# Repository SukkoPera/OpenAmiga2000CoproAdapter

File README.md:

# OpenAmiga2000CoproAdapter
OpenAmiga2000CoproAdapter is an Open Hardware adapter that allows installing the main processor of a Commodore Amiga 2000 computer in the co-processor slot.

### Summary
OpenAmiga2000CoproAdapter is an adapter that allows installing the main processor of a Commodore Amiga 2000 computer in the co-processor slot, based on [work by kipper2k](http://eab.abime.net/showthread.php?t=89604). It is mainly useful to mount TerribleFire and other accelerator cards without having to remove the floppy drive tray and without having them bump into your MegaChip, in case.

The adapter is very similar to the original, except that I skipped the INT7 and the A600 NMI circuits. Those are not needed for TerribleFire cards and for most other boards (I think they are for Vampires only). I carried over the INT2/OVR header, since the former is needed for the TF530. I have also introduced solder jumpers for the FR0-2 signals: those are not connected on kipper2k's board, I don't know why and it works well anyway, but I thought they wouldn't hurt as they will be open by default.

You may be able to install this without removing the original CPU by cutting the E jumper and closing the BOSS one.

This is a slightly expensive board to manufacture because it exceeds the 10x10cm limit that cheap fab houses impose, because it needs gold-plating for better contact and resistance to repeated insertions/removals, and because the edge connector should be beveled to ease insertion. These are the recommended settings if you want to get the boards made.

### Installation
**Please be very careful when plugging this board** in the co-processor slot: there is an arrow on the board, **it must point to the back of the Amiga**. Plugging this adapter backwards will damage your CPU/accelerator card, as some pins of the CPU slot carry +12V!

When this board is installed, most likely the original 68000 socket must be left empty unless you cut the E jumper and close the BOSS jumper, though this ultimately depends on the particular card you will be installing.

### License
The OpenAmiga2000CoproAdapter documentation, including the design itself, is copyright &copy; SukkoPera 2018-2019.

OpenAmiga2000CoproAdapter is Open Hardware licensed under the [CERN OHL v. 1.2](http://ohwr.org/cernohl).

You may redistribute and modify this documentation under the terms of the CERN OHL v.1.2. This documentation is distributed *as is* and WITHOUT ANY EXPRESS OR IMPLIED WARRANTIES whatsoever with respect to its functionality, operability or use, including, without limitation, any implied warranties OF MERCHANTABILITY, SATISFACTORY QUALITY, FITNESS FOR A PARTICULAR PURPOSE or infringement. We expressly disclaim any liability whatsoever for any direct, indirect, consequential, incidental or special damages, including, without limitation, lost revenues, lost profits, losses resulting from business interruption or loss of data, regardless of the form of action or legal theory under which the liability may be asserted, even if advised of the possibility or likelihood of such damages.

A copy of the full license is included in file [LICENSE.pdf](LICENSE.pdf), please refer to it for applicable conditions. In order to properly deal with its terms, please see file [LICENSE_HOWTO.pdf](LICENSE_HOWTO.pdf).

The contact points for information about manufactured Products (see section 4.2) are listed in file [PRODUCT.md](PRODUCT.md).

Any modifications made by Licensees (see section 3.4.b) shall be recorded in file [CHANGES.md](CHANGES.md).

The Documentation Location of the original project is https://github.com/SukkoPera/OpenAmiga2000CoproAdapter/.

### Support the Project
Since the project is open you are free to get the PCBs made by your preferred manufacturer, however in case you want to support the development, you can order them from PCBWay through this link:

You get cheap, professionally-made and good quality PCBs, I get some credit that will help with this and [other projects](https://www.pcbway.com/project/member/shareproject/?bmbid=41100). You won't even have to worry about the various PCB options, it's all pre-configured for you!

Also, if you still have to register to that site, [you can use this link](https://www.pcbway.com/setinvite.aspx?inviteid=41100) to get some bonus initial credit (and yield me some more).

Again, if you want to use another manufacturer, feel free to, don't feel obligated :). But then you can buy me a coffee if you want:

### Get Help
If you need help or have questions, you can join [the official Telegram group](https://t.me/joinchat/HUHdWBC9J9JnYIrvTYfZmg).

### Thanks
Thanks to kipper2k, of course :).

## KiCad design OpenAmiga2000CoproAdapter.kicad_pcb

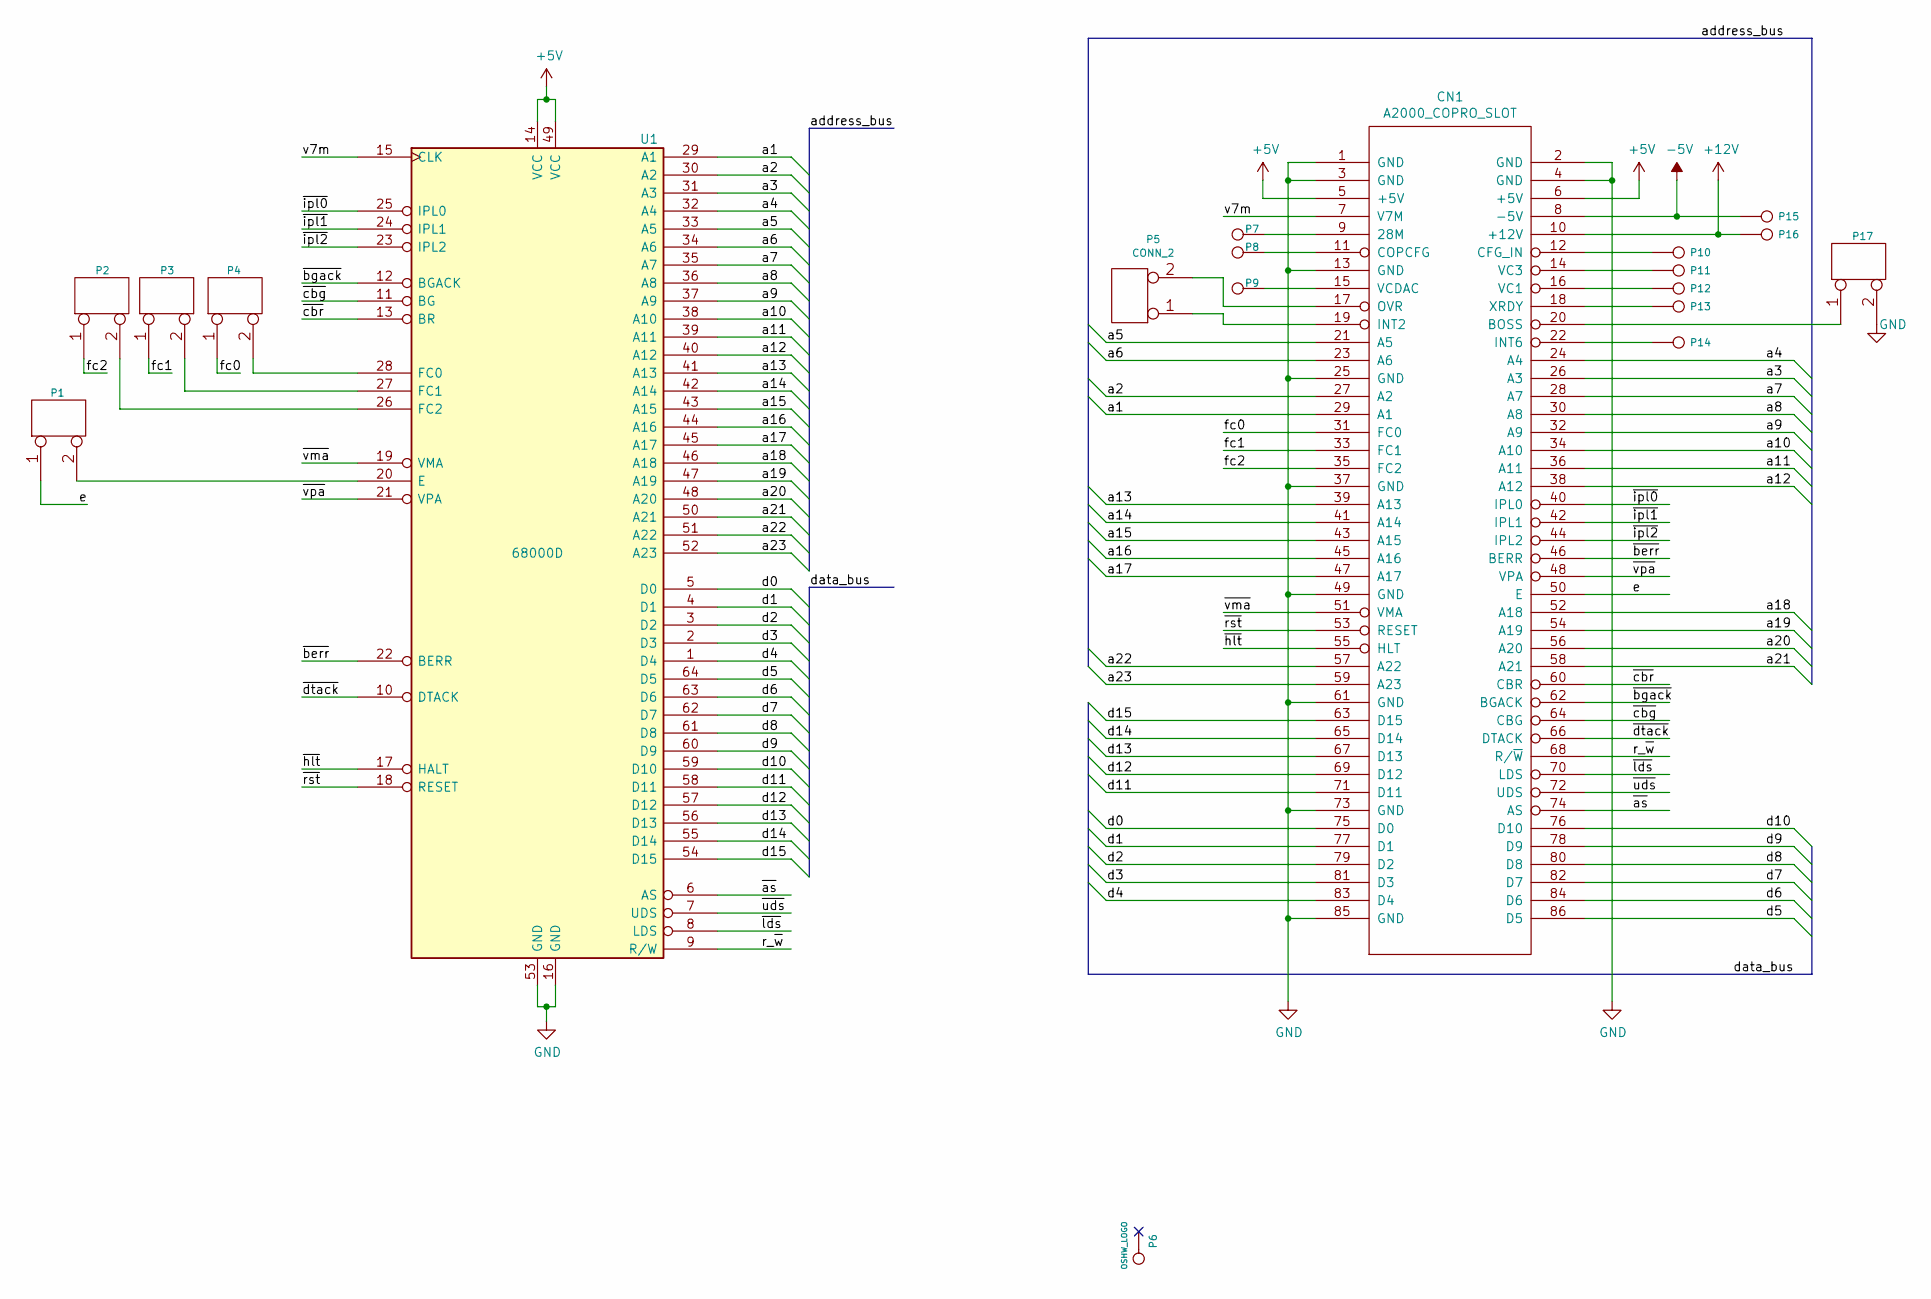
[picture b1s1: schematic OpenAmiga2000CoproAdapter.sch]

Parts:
CN1: A2000_COPRO_SLOT
P1: CONN_2; SolderJumper-2_P1.3mm_Bridged_RoundedPad1.0x1.5mm
P2, P3, P4, P17: CONN_2; SolderJumper-2_P1.3mm_Open_RoundedPad1.0x1.5mm
P5: CONN_2; PinHeader_1x02_P2.54mm_Vertical
P6: OSHW_LOGO; OSHW-Logo_7.5x8mm_Copper
P7, P8, P9, P10, P11, P12, P13, P14, P15, P16: CONN_1; TestPoint_Pad_D1.5mm
U1: 68000D; DIP-64_W22.86mm_Socket_LongPads

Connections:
+5V: CN1.5 (+5V), CN1.6 (+5V), U1.14 (VCC), U1.49 (VCC)
+12V: CN1.10 (+12V), P16.1
-5V: CN1.8 (-5V), P15.1
/a1: CN1.29 (A1), U1.29 (A1)
/a2: CN1.27 (A2), U1.30 (A2)
/a3: CN1.26 (A3), U1.31 (A3)
/a4: CN1.24 (A4), U1.32 (A4)
/a5: CN1.21 (A5), U1.33 (A5)
/a6: CN1.23 (A6), U1.34 (A6)
/a7: CN1.28 (A7), U1.35 (A7)
/a8: CN1.30 (A8), U1.36 (A8)
/a9: CN1.32 (A9), U1.37 (A9)
/a10: CN1.34 (A10), U1.38 (A10)
/a11: CN1.36 (A11), U1.39 (A11)
/a12: CN1.38 (A12), U1.40 (A12)
/a13: CN1.39 (A13), U1.41 (A13)
/a14: CN1.41 (A14), U1.42 (A14)
/a15: CN1.43 (A15), U1.43 (A15)
/a16: CN1.45 (A16), U1.44 (A16)
/a17: CN1.47 (A17), U1.45 (A17)
/a18: CN1.52 (A18), U1.46 (A18)
/a19: CN1.54 (A19), U1.47 (A19)
/a20: CN1.56 (A20), U1.48 (A20)
/a21: CN1.58 (A21), U1.50 (A21)
/a22: CN1.57 (A22), U1.51 (A22)
/a23: CN1.59 (A23), U1.52 (A23)
/d0: CN1.75 (D0), U1.5 (D0)
/d1: CN1.77 (D1), U1.4 (D1)
/d2: CN1.79 (D2), U1.3 (D2)
/d3: CN1.81 (D3), U1.2 (D3)
/d4: CN1.83 (D4), U1.1 (D4)
/d5: CN1.86 (D5), U1.64 (D5)
/d6: CN1.84 (D6), U1.63 (D6)
/d7: CN1.82 (D7), U1.62 (D7)
/d8: CN1.80 (D8), U1.61 (D8)
/d9: CN1.78 (D9), U1.60 (D9)
/d10: CN1.76 (D10), U1.59 (D10)
/d11: CN1.71 (D11), U1.58 (D11)
/d12: CN1.69 (D12), U1.57 (D12)
/d13: CN1.67 (D13), U1.56 (D13)
/d14: CN1.65 (D14), U1.55 (D14)
/d15: CN1.63 (D15), U1.54 (D15)
/e: CN1.50 (E), P1.1
/fc0: CN1.31 (FC0), P4.1
/fc1: CN1.33 (FC1), P3.1
/fc2: CN1.35 (FC2), P2.1
/r_~w: CN1.68 (R/~W), U1.9 (R/W)
/v7m: CN1.7 (V7M), U1.15 (CLK)
/~as: CN1.74 (AS), U1.6 (AS)
/~berr: CN1.46 (BERR), U1.22 (BERR)
/~bgack: CN1.62 (BGACK), U1.12 (BGACK)
/~cbg: CN1.64 (CBG), U1.11 (BG)
/~cbr: CN1.60 (CBR), U1.13 (BR)
/~dtack: CN1.66 (DTACK), U1.10 (DTACK)
/~hlt: CN1.55 (HLT), U1.17 (HALT)
/~ipl0: CN1.40 (IPL0), U1.25 (IPL0)
/~ipl1: CN1.42 (IPL1), U1.24 (IPL1)
/~ipl2: CN1.44 (IPL2), U1.23 (IPL2)
/~lds: CN1.70 (LDS), U1.8 (LDS)
/~rst: CN1.53 (RESET), U1.18 (RESET)
/~uds: CN1.72 (UDS), U1.7 (UDS)
/~vma: CN1.51 (VMA), U1.19 (VMA)
/~vpa: CN1.48 (VPA), U1.21 (VPA)
GND: CN1.1 (GND), CN1.2 (GND), CN1.3 (GND), CN1.4 (GND), CN1.13 (GND), CN1.25 (GND), CN1.37 (GND), CN1.49 (GND), CN1.61 (GND), CN1.73 (GND), CN1.85 (GND), P17.2 (PM), U1.16 (GND), U1.53 (GND)
unnamed: CN1.9 (28M), P7.1
unnamed: CN1.11 (COPCFG), P8.1
unnamed: CN1.12 (CFG_IN), P10.1
unnamed: CN1.14 (VC3), P11.1
unnamed: CN1.15 (VCDAC), P9.1
unnamed: CN1.16 (VC1), P12.1
unnamed: CN1.17 (OVR), P5.2 (PM)
unnamed: CN1.18 (XRDY), P13.1
unnamed: CN1.19 (INT2), P5.1
unnamed: CN1.20 (BOSS), P17.1
unnamed: CN1.22 (INT6), P14.1
unnamed: P1.2 (PM), U1.20 (E)
unnamed: P2.2 (PM), U1.26 (FC2)
unnamed: P3.2 (PM), U1.27 (FC1)
unnamed: P4.2 (PM), U1.28 (FC0)

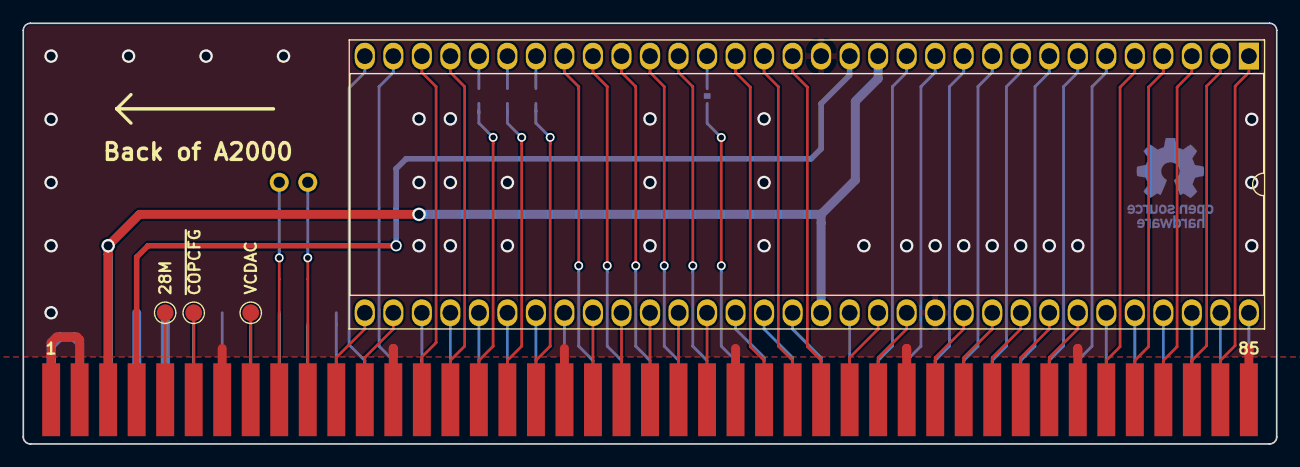
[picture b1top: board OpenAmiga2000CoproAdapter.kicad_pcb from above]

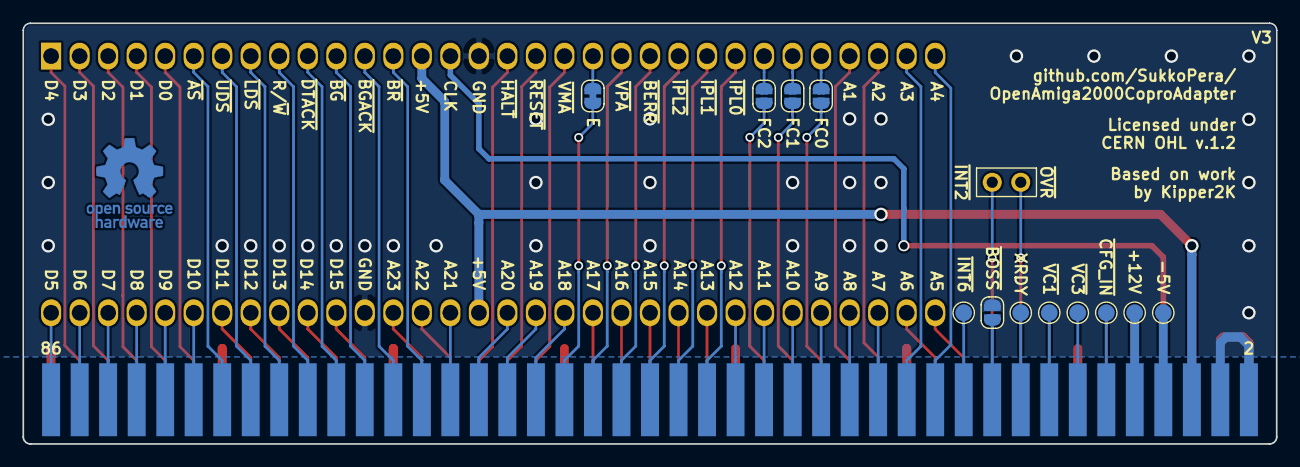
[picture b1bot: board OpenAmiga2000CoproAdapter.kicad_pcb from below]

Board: 2 copper layers, 111.6 x 37.5 mm, 19 parts (14 on the bottom side), 79 nets.

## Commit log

2018-10-28 Initial commit, V1 sent to production
2018-10-29 Add silkscreen hint for the FCx lines
2018-10-30 Nicer placement of +5V/Clock traces
2018-11-02 Improve 3D view
2018-11-02 Update images
2019-02-11 Add license info
2019-02-11 Erm, fix README.md
2019-02-12 Add pin names on silkscreen Yeah, I like this!
2019-02-13 Add A500/A2000 Technical Reference Manual
2019-02-14 Treat CONFIG_IN pin properly
2019-02-14 Add test points for *all* the signals available on the connector
2019-02-14 Minor cosmetic fixes
2019-02-14 More minor cosmetic fixes
2019-03-21 Make board ~0.4mm narrower for a better fit
2019-07-09 Ready for V3
2021-02-02 Add jumpers for E, Boss
    * Cutting the E jumper and closing the BOSS one will allow the card to work without removing the original cpu
    * Closing BOSS is required for B2000 DMA to work, buster doesn't route BR to the copro slot unless /BOSS is asserted

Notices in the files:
OpenAmiga2000CoproAdapter.kicad_pcb:
Licensed under CERN OHL v.1.2
